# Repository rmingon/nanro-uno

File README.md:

# ATmega88PA Sensor Interface Board

This project is a compact microcontroller development board based on the **ATmega88PA**, equipped with an **MPU-6050** accelerometer/gyroscope and USB interface. It is designed for embedded systems development, particularly in motion-sensing or robotics applications.

## Features

- **Microcontroller**: ATmega88PA (TQFP32)
- **IMU Sensor**: MPU-6050 (3-axis gyroscope + 3-axis accelerometer)
- **USB Interface**: CH340C USB-to-Serial converter
- **Onboard Voltage Regulation**: 5V to 3.3V via AP2112K-3.3
- **USB Power and Data via Micro-USB**
- **External Programming Header (ISP)**
- **I2C and UART breakout pins**
- **Reset and User Button**
- **LED Indicators**: Power and status/debug
- **Crystal Oscillator**: 8 MHz external crystal
- **Compact, breadboard-friendly form factor**

---

## Schematic Overview

- **Power Supply**:
  - Micro-USB supplies +5V.
  - LDO (AP2112K-3.3) regulates down to +3.3V for MPU-6050 and I/O.
- **Microcontroller (U2)**: ATmega88PA is the central controller.
  - Interfaces: I2C (SCL/SDA), UART (TX/RX), and SPI (MISO/MOSI/SCK)
  - Reset circuitry via pushbutton and capacitor.
- **MPU-6050 (U4)**: Connected via I2C with 4.7kΩ pull-ups.
- **USB to Serial (U3 - CH340C)**:
  - Used for serial communication and programming via UART.
- **ISP Header (J1)**: For initial bootloader flashing or full firmware flashing.

---

## PCB Details

- **2-layer PCB** with top and bottom copper planes.
- Carefully routed signal traces with decoupling capacitors close to ICs.
- Exposed pads for easy pin access to GPIOs.
- Mounting holes and labeled pin headers.
- Silkscreen labeling of pin functions for ease of use.
- 3D Render available for visualization and placement inspection.

---

## Pinout Summary

| Pin | Function       | Notes                      |
|-----|----------------|----------------------------|
| PB0–PB7 | GPIO / UART / SPI | Digital I/O and communication |
| PC0–PC5 | GPIO / I2C        | Includes SDA/SCL for MPU6050 |
| PD0–PD7 | GPIO / UART       | TX/RX, user-defined GPIO      |
| SW1     | Reset Button      | Pull-down with 10kΩ resistor |
| SW2     | User Button       | Connected to PB0              |
| J1      | ISP Header        | MISO/MOSI/SCK/RESET          |

---

## Getting Started

### 1. Flashing Firmware

- **Via ISP (J1)**: Use AVR ISP programmer.
- **Via UART (CH340C)**: Use bootloader (if pre-installed).

### 2. Power Supply

- Plug in via **Micro-USB**.
- Onboard LDO provides 3.3V logic supply.

### 3. I2C Communication

- MPU-6050 is accessible at default I2C address `0x68`.
- Ensure pull-ups (R3, R4 = 4.7kΩ) are present on SDA/SCL lines.

---

## Tools Used

- **Schematic & PCB Design**: [KiCad EDA](https://kicad.org)
- **Microcontroller Programming**: `avrdude`, `Arduino as ISP`, PlatformIO
- **Firmware Development**: C/C++ (AVR-GCC or Arduino IDE)

---

## License

Open-source hardware. You may use, modify, and distribute under the terms of the  MIT license.

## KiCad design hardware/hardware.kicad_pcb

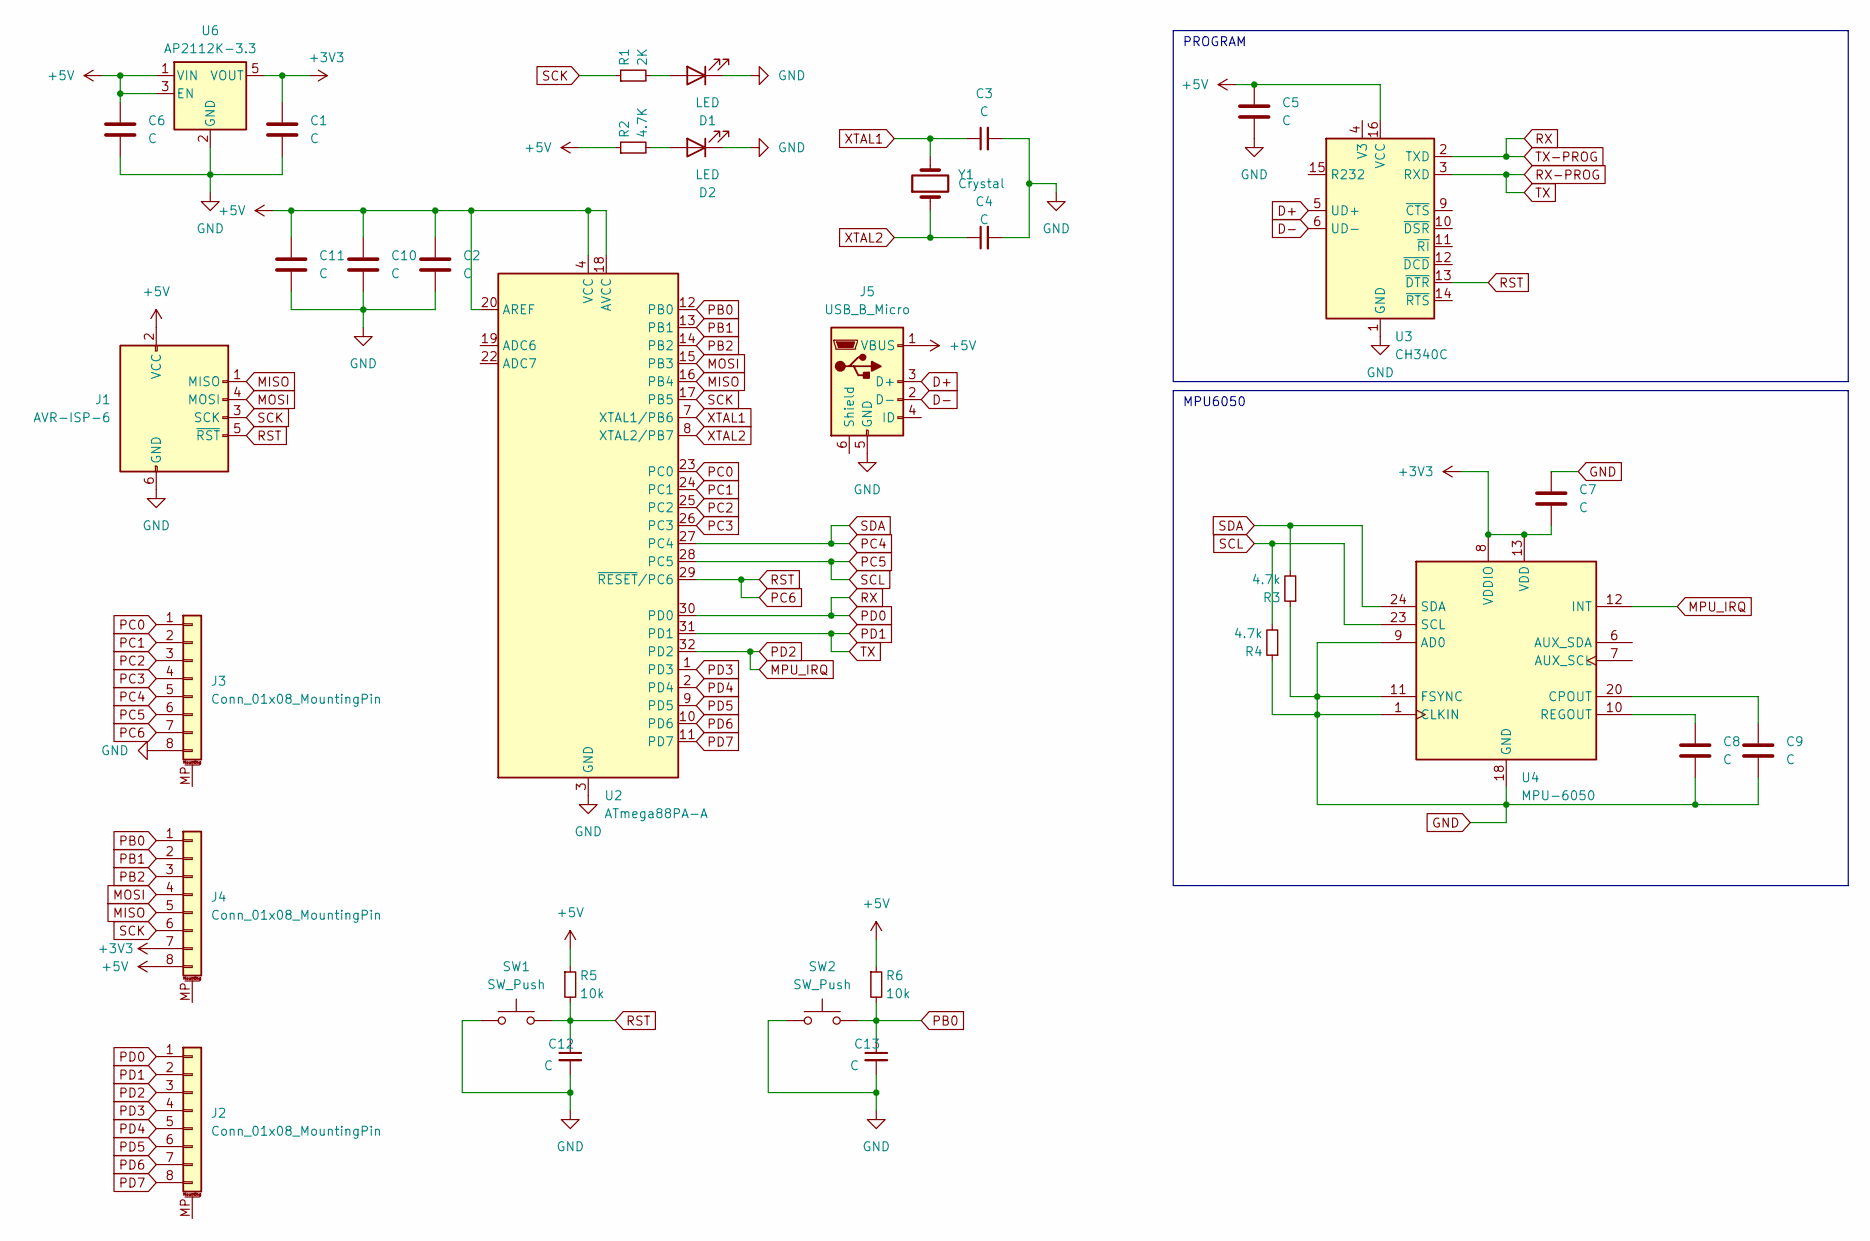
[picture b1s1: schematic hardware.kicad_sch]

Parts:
C1, C6, C10: C; C_0603_1608Metric; LCSC C14858
C2, C7, C11, C12, C13: C; C_0603_1608Metric; LCSC C5137611
C3, C4, C5: C; C_0603_1608Metric; LCSC C106245
C8: C; C_0603_1608Metric; LCSC C1322361
C9: C; C_0603_1608Metric; LCSC C1604
D1: LED; D_0603_1608Metric; LCSC C965799
D2: LED; D_0603_1608Metric; LCSC C965807
J1: AVR-ISP-6; PinHeader_2x03_P1.00mm_Vertical
J2, J3, J4: Conn_01x08_MountingPin; PinHeader_1x08_P2.54mm_Vertical
J5: USB_B_Micro; USB_Micro-B_GCT_USB3076-30-A; LCSC C6007475
R1: 2K; R_0603_1608Metric; LCSC C22975
R2: 4.7K; R_0603_1608Metric; LCSC C99782
R3, R4: 4.7k; R_0603_1608Metric; LCSC C99782
R5, R6: 10k; R_0603_1608Metric; LCSC C2930027
SW1, SW2: SW_Push; SW_Push_SPST_NO_Alps_SKRK; LCSC C115357
U2: ATmega88PA-A; TQFP-32_7x7mm_P0.8mm; LCSC C8727
U3: CH340C; SOIC-16_3.9x9.9mm_P1.27mm; LCSC C84681
U4: MPU-6050; InvenSense_QFN-24_4x4mm_P0.5mm; LCSC C24112
U6: AP2112K-3.3; SOT-23-5; LCSC C51118
Y1: Crystal; Crystal_SMD_3225-4Pin_3.2x2.5mm; LCSC C2682775

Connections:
+3V3: C1.1, C7.2, J4.7, U4.8 (VDDIO), U4.13 (VDD), U6.5 (VOUT)
+5V: C2.1, C5.1, C6.1, C10.1, C11.1, J1.2 (VCC), J4.8, J5.1 (VBUS), R2.1, R5.1, R6.1, U2.4 (VCC), U2.6 (VCC), U2.18 (AVCC), U2.20 (AREF), U3.16 (VCC), U6.1 (VIN), U6.3 (EN)
D+: J5.3 (D+), U3.5 (UD+)
D-: J5.2 (D-), U3.6 (UD-)
GND: C1.2, C2.2, C3.2, C4.2, C5.2, C6.2, C7.1, C8.2, C9.2, C10.2, C11.2, C12.2, C13.2, D1.1 (K), D2.1 (K), J1.6 (GND), J3.8, J5.5 (GND), R3.1, R4.1, SW1.1, SW2.1, U2.3 (GND), U2.5 (GND), U2.21 (GND), U3.1 (GND), U4.1 (CLKIN), U4.9 (AD0), U4.11 (FSYNC), U4.18 (GND), U6.2 (GND)
MISO: J1.1 (MISO), J4.5, U2.16 (PB4)
MOSI: J1.4 (MOSI), J4.4, U2.15 (PB3)
MPU_IRQ: J2.3, U2.32 (PD2), U4.12 (INT)
unnamed: D1.2 (A), R1.2
unnamed: D2.2 (A), R2.2
unnamed: C9.1, U4.20 (CPOUT)
unnamed: C8.1, U4.10 (REGOUT)
PB0: C13.1, J4.1, R6.2, SW2.2, U2.12 (PB0)
PB1: J4.2, U2.13 (PB1)
PB2: J4.3, U2.14 (PB2)
PC0: J3.1, U2.23 (PC0)
PC1: J3.2, U2.24 (PC1)
PC2: J3.3, U2.25 (PC2)
PC3: J3.4, U2.26 (PC3)
PC4: J3.5, R3.2, U2.27 (PC4), U4.24 (SDA)
PC5: J3.6, R4.2, U2.28 (PC5), U4.23 (SCL)
PC6: C12.1, J1.5 (~RST), J3.7, R5.2, SW1.2, U2.29 (~RESET/PC6), U3.13 (~DTR)
PD0: J2.1, U2.30 (PD0), U3.2 (TXD)
PD1: J2.2, U2.31 (PD1), U3.3 (RXD)
PD3: J2.4, U2.1 (PD3)
PD4: J2.5, U2.2 (PD4)
PD5: J2.6, U2.9 (PD5)
PD6: J2.7, U2.10 (PD6)
PD7: J2.8, U2.11 (PD7)
SCK: J1.3 (SCK), J4.6, R1.1, U2.17 (PB5)
XTAL1: C3.1, U2.7 (XTAL1/PB6), Y1.2
XTAL2: C4.1, U2.8 (XTAL2/PB7), Y1.1

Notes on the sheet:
MPU6050
PROGRAM

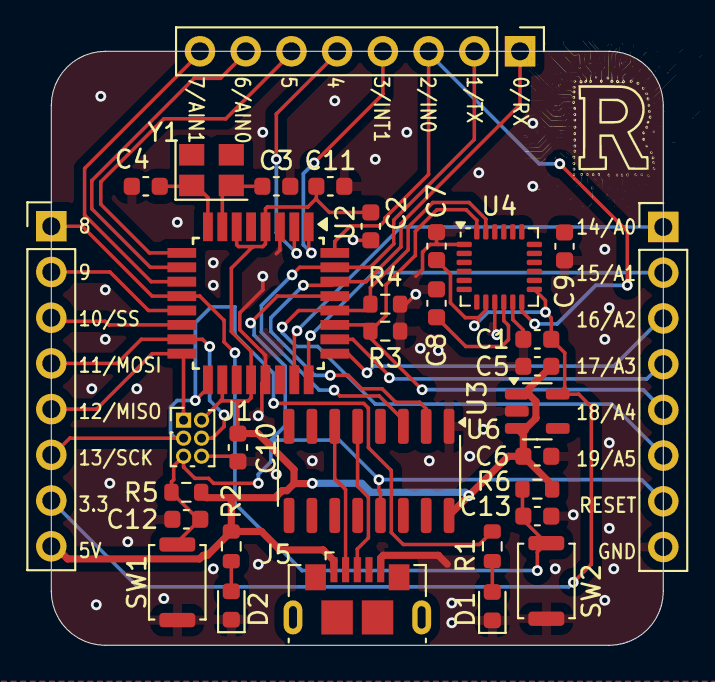
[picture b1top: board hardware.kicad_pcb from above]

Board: 2 copper layers, 34.0 x 33.0 mm, 33 parts (0 on the bottom side), 32 nets.

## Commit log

2025-05-26 finish wiring
2025-05-26 add pictures
2025-05-26 add readme
2025-05-26 update parts lcsc
2025-05-27 fix user button capacitor ground
